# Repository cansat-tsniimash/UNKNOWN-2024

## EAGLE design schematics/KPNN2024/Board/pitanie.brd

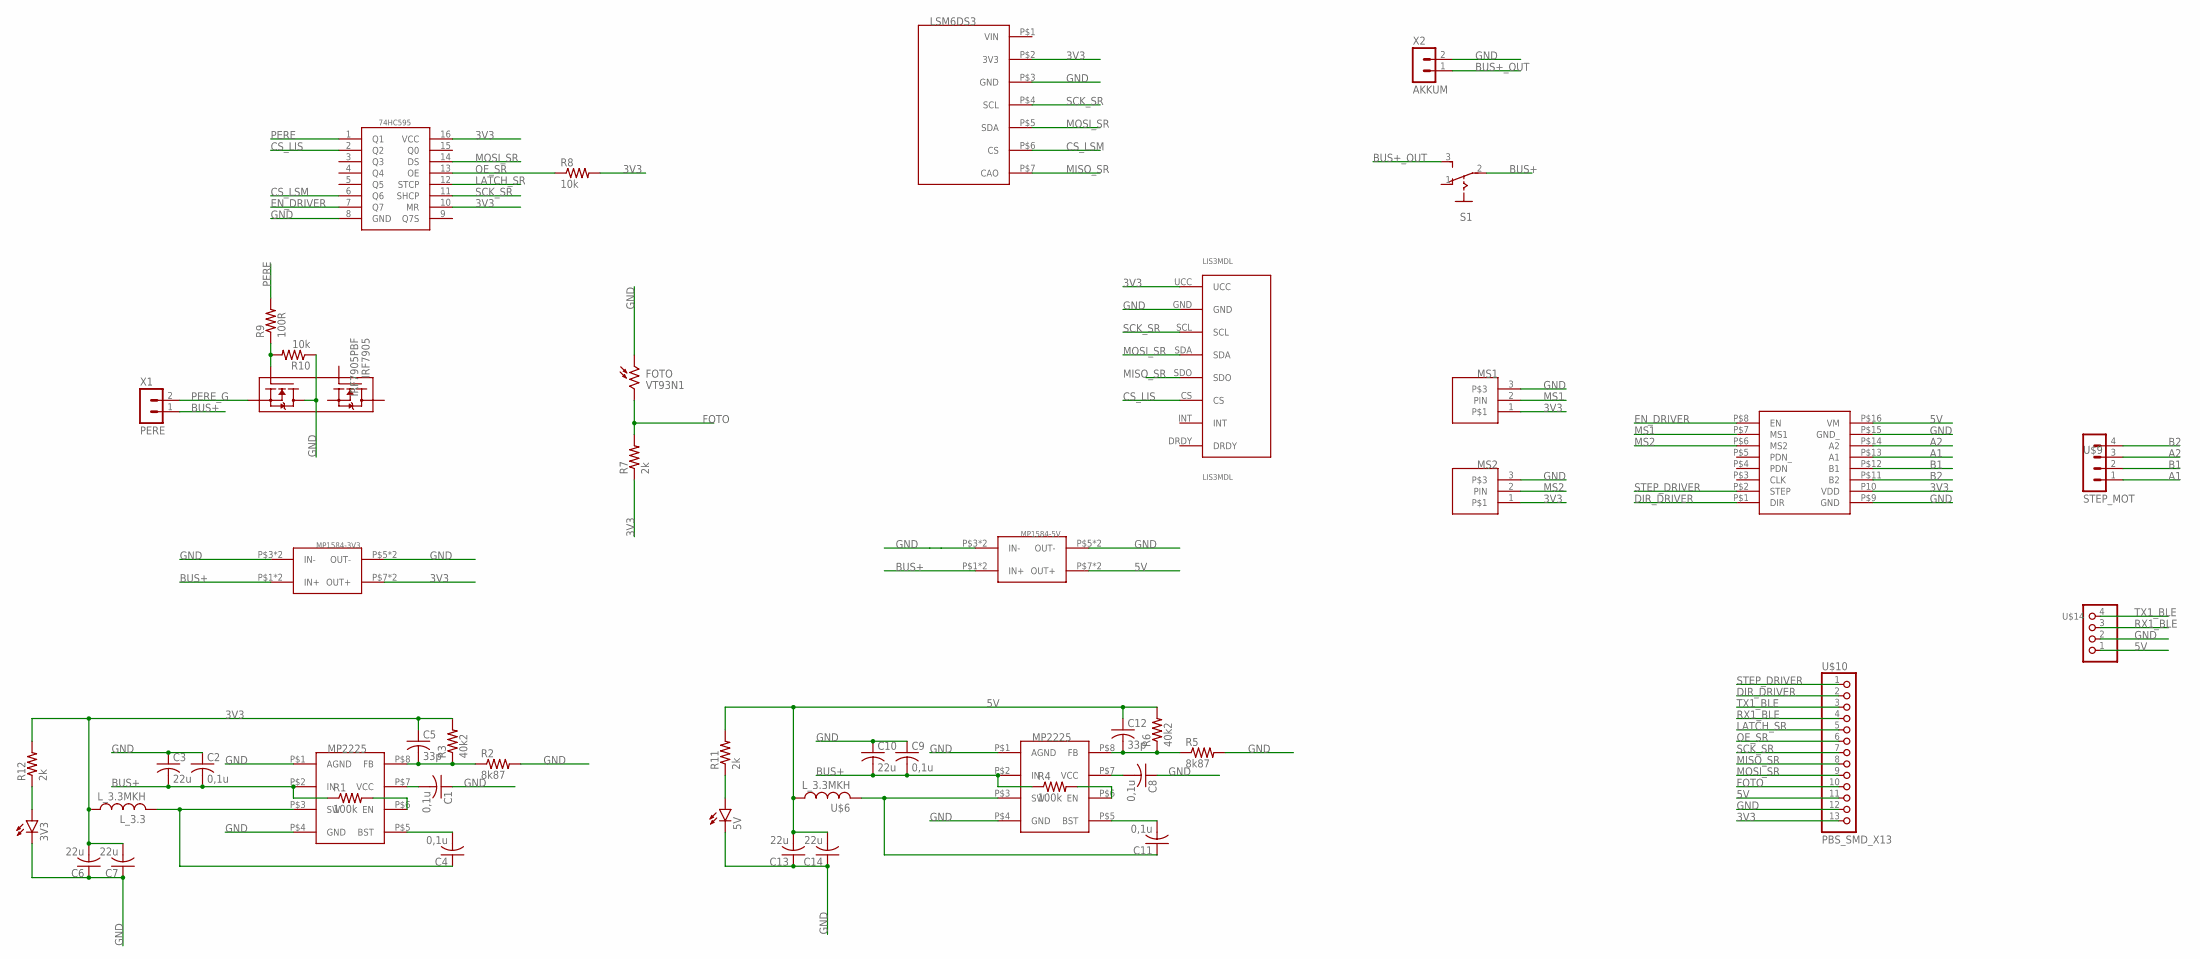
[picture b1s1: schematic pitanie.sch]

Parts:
3V3, 5V: LEDCHIP-LED0603; CHIP-LED0603
74HC595: 74HC595; TSSOP16
C1, C4, C8, C11: 0,1u; C0603
C2, C9: 0,1u; C1206
C3, C10: 22u; C0603
C5, C12: 33p; C0603
C6, C7, C13, C14: 22u; C1206
DRIVER: TMC2209_WITHOUT
FOTO: VT93N1
IRF7905: IRF7905PBF; SO8
LIS3MDL: LIS3MDL
LSM6DS3: LSM6DS3_WITHOUT
L_3.3: L_3.3MKH; L_SPM5020
MP1584-3V3: MP1584-B
MP1584-5V: MP1584; MP1584-B
MS1, MS2: CONNECT_3
R1, R4: 100k; R0603
R2, R5: 8k87; R0603
R3, R6: 40k2; R0603
R7, R11, R12: 2k; R0603
R8, R10: 10k; R0603
R9: 100R; R0603
S1: UNICS-SWITCHSS_12D11; SS_12D11
U$2, U$5: MP2225; TSOT23-8
U$6: L_3.3MKH; L_SPM5020
U$9: STEP_MOT; JST-4-2.5
U$10: PBS_SMD_X13; PBD_SMD_X13
U$14: BLUETOOTH; 53047-04
X1: PERE; JST-2-2.5
X2: AKKUM; JST-2-2.5

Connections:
3V3: 74HC595.10 (MR), 74HC595.16 (VCC), C5.1, C6.2, C7.2, DRIVER.P10 (VDD), LIS3MDL.UCC, LSM6DS3.P$2 (3V3), L_3.3.P$1 (1), MP1584-3V3.P$7 (OUT+), MP1584-3V3.P$8 (OUT+), MS1.1, MS2.1, R3.2, R7.1, R8.2, R12.2, U$10.13
5V: C12.1, C13.2, C14.2, DRIVER.P$16 (VM), MP1584-5V.P$7 (OUT+), MP1584-5V.P$8 (OUT+), R6.2, R11.2, U$6.P$1 (1), U$10.11, U$14.1
A1: DRIVER.P$13 (A1), U$9.1
A2: DRIVER.P$14 (A2), U$9.3
B1: DRIVER.P$12 (B1), U$9.2
B2: DRIVER.P$11 (B2), U$9.4
BUS+: C2.2, C3.2, C9.2, C10.2, MP1584-3V3.P$1 (IN+), MP1584-3V3.P$2 (IN+), MP1584-5V.P$1 (IN+), MP1584-5V.P$2 (IN+), R1.1, R4.1, S1.2, U$2.P$2 (IN), U$5.P$2 (IN), X1.1
BUS+_OUT: S1.3 (S), X2.1
CS_LIS: 74HC595.2 (Q2), LIS3MDL.CS
CS_LSM: 74HC595.6 (Q6), LSM6DS3.P$6 (CS)
DIR_DRIVER: DRIVER.P$1 (DIR), U$10.2
EN_DRIVER: 74HC595.7 (Q7), DRIVER.P$8 (EN)
FOTO: FOTO.P$2 (2), R7.2, U$10.10
GND: 3V3.C, 5V.C, 74HC595.8 (GND), C1.1, C2.1, C3.1, C6.1, C7.1, C8.1, C9.1, C10.1, C13.1, C14.1, DRIVER.P$9 (GND), DRIVER.P$15 (GND_), FOTO.P$1 (1), IRF7905.7 (D2), IRF7905.8 (D2), LIS3MDL.GND, LSM6DS3.P$3 (GND), MP1584-3V3.P$3 (IN-), MP1584-3V3.P$4 (IN-), MP1584-3V3.P$5 (OUT-), MP1584-3V3.P$6 (OUT-), MP1584-5V.P$3 (IN-), MP1584-5V.P$4 (IN-), MP1584-5V.P$5 (OUT-), MP1584-5V.P$6 (OUT-), MS1.3, MS2.3, R2.2, R5.2, R10.1, U$2.P$1 (AGND), U$2.P$4 (GND), U$5.P$1 (AGND), U$5.P$4 (GND), U$10.12, U$14.2, X2.2
LATCH_SR: 74HC595.12 (STCP), U$10.5
MISO_SR: LIS3MDL.SDO, LSM6DS3.P$7 (CAO), U$10.8
MOSI_SR: 74HC595.14 (DS), LIS3MDL.SDA, LSM6DS3.P$5 (SDA), U$10.9
MS1: DRIVER.P$7 (MS1), MS1.2 (PIN)
MS2: DRIVER.P$6 (MS2), MS2.2 (PIN)
unnamed: C1.2, U$2.P$7 (VCC)
unnamed: R1.2, U$2.P$6 (EN)
unnamed: C4.2, U$2.P$5 (BST)
unnamed: C4.1, L_3.3.P$2 (2), U$2.P$3 (SW)
unnamed: C5.2, R2.1, R3.1, U$2.P$8 (FB)
unnamed: IRF7905.2 (G2), R9.1, R10.2
unnamed: C8.2, U$5.P$7 (VCC)
unnamed: R4.2, U$5.P$6 (EN)
unnamed: C11.2, U$5.P$5 (BST)
unnamed: C11.1, U$5.P$3 (SW), U$6.P$2 (2)
unnamed: C12.2, R5.1, R6.1, U$5.P$8 (FB)
unnamed: 5V.A, R11.1
unnamed: 3V3.A, R12.1
OE_SR: 74HC595.13 (OE), R8.1, U$10.6
PERE: 74HC595.1 (Q1), R9.2
PERE_G: IRF7905.1 (S2), X1.2
RX1_BLE: U$10.4, U$14.3
SCK_SR: 74HC595.11 (SHCP), LIS3MDL.SCL, LSM6DS3.P$4 (SCL), U$10.7
STEP_DRIVER: DRIVER.P$2 (STEP), U$10.1
TX1_BLE: U$10.3, U$14.4

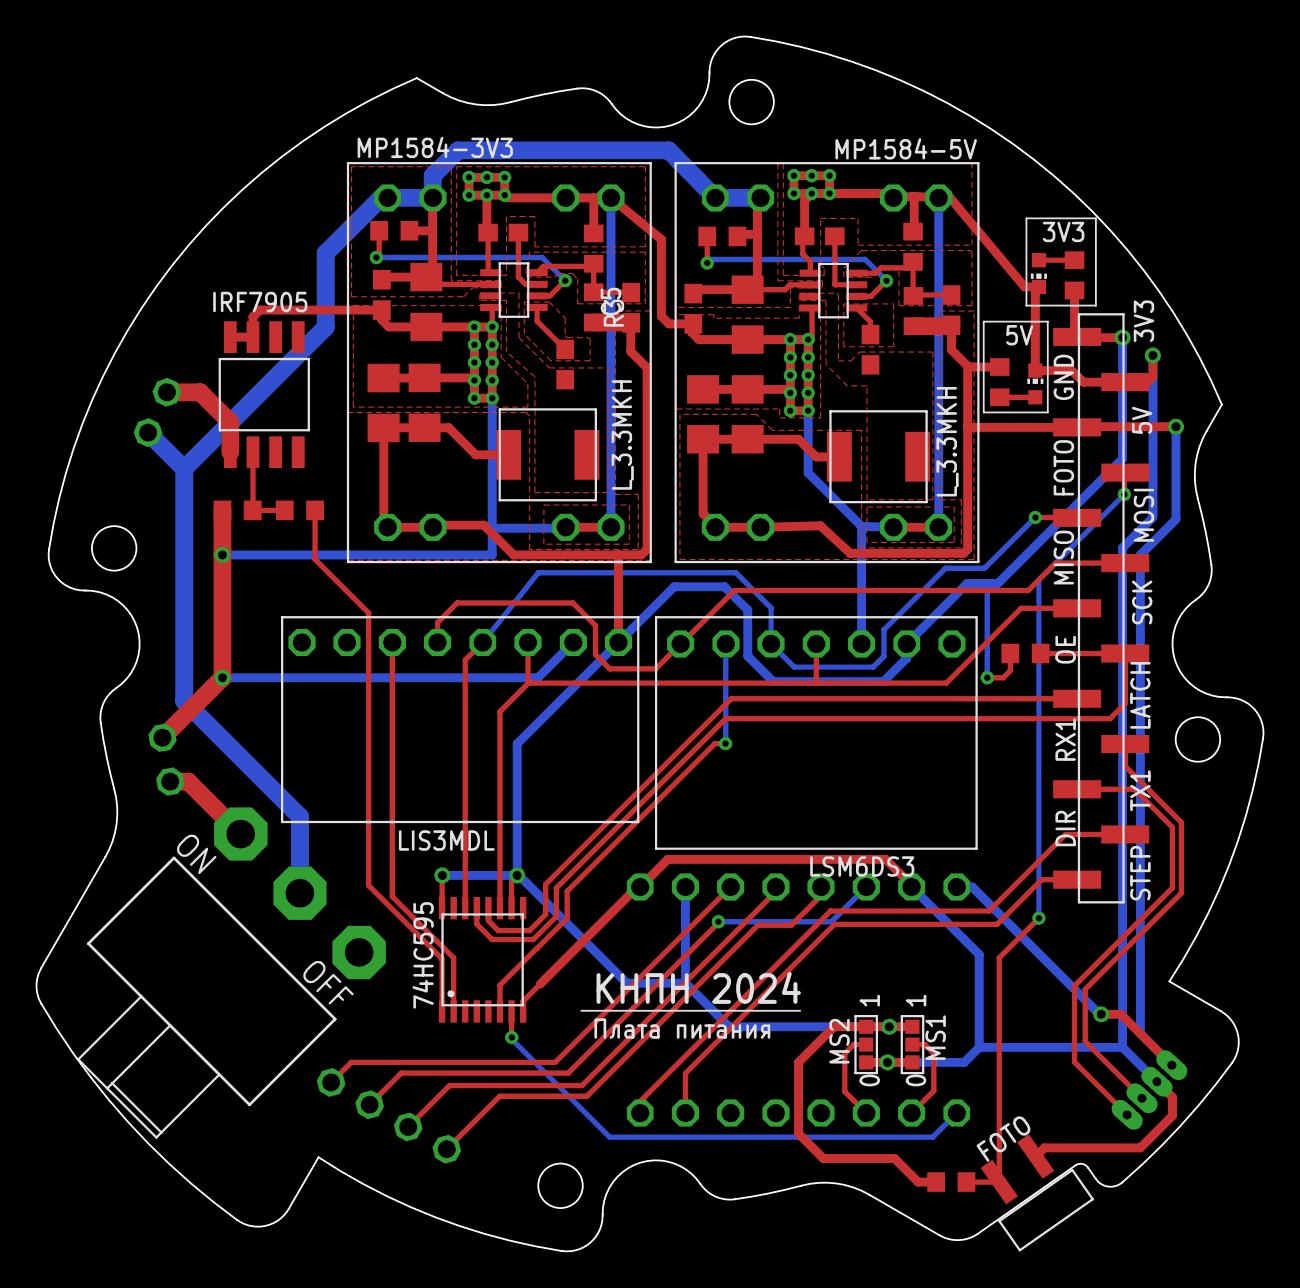
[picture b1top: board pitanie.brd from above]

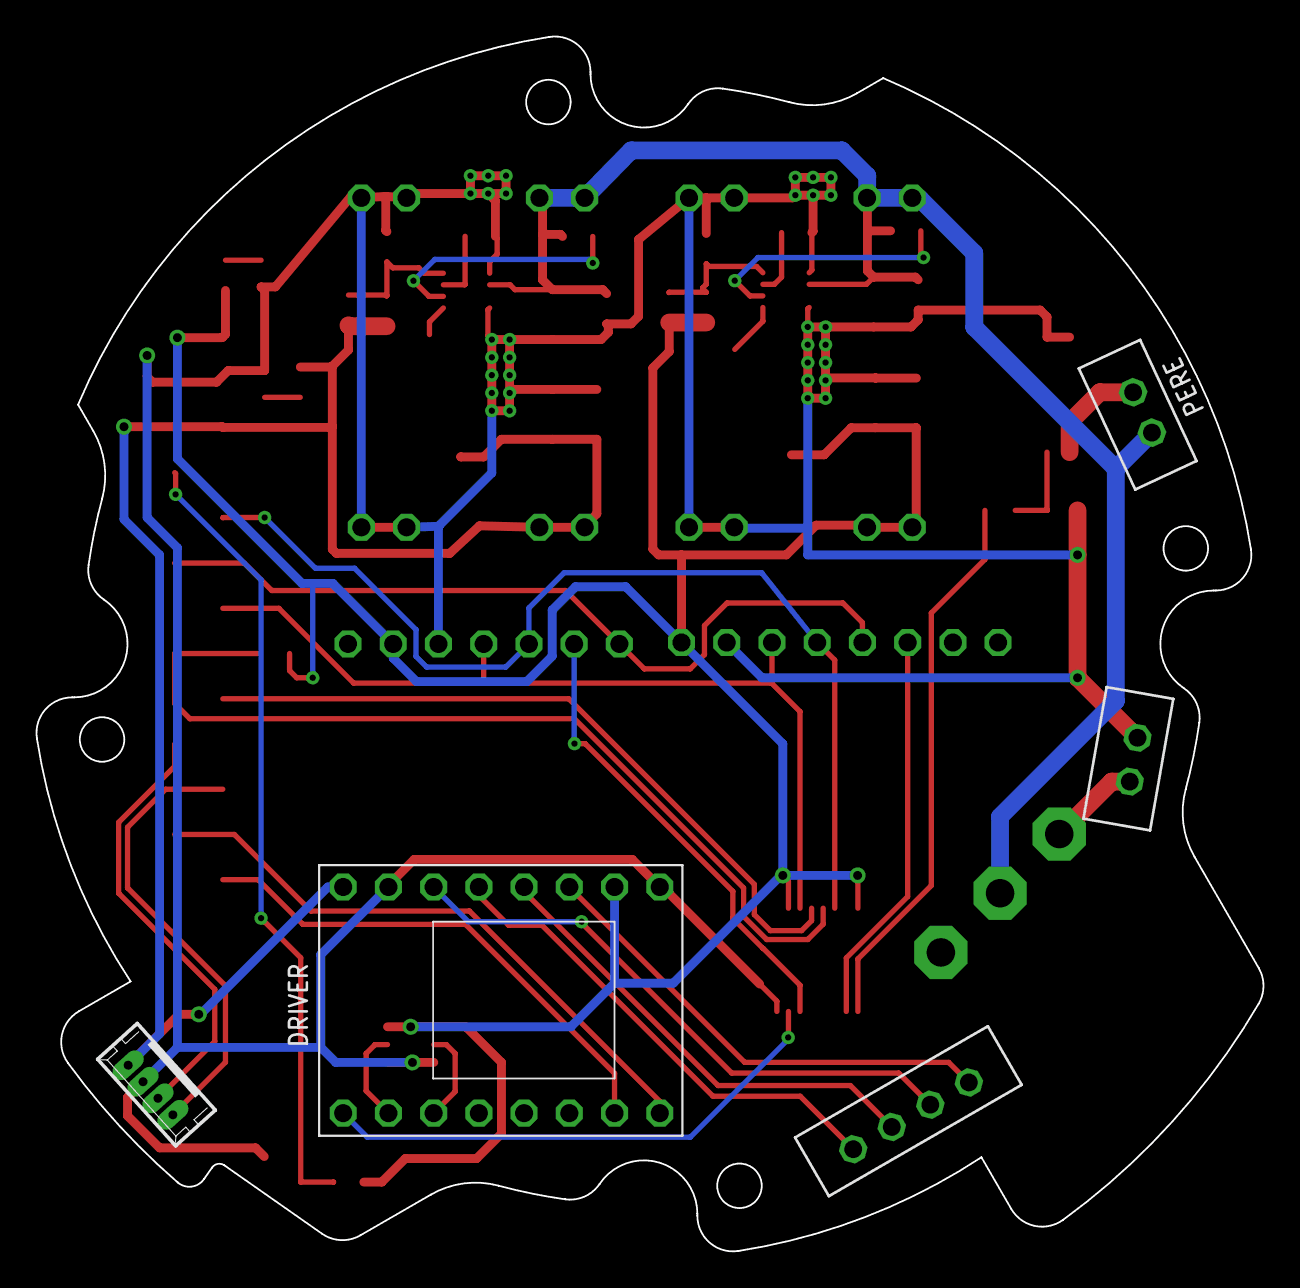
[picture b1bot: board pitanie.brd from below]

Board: 2 copper layers, 68.9 x 68.2 mm, 49 parts (5 on the bottom side), 39 nets.

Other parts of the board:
U$1: Плата питания; LOGO

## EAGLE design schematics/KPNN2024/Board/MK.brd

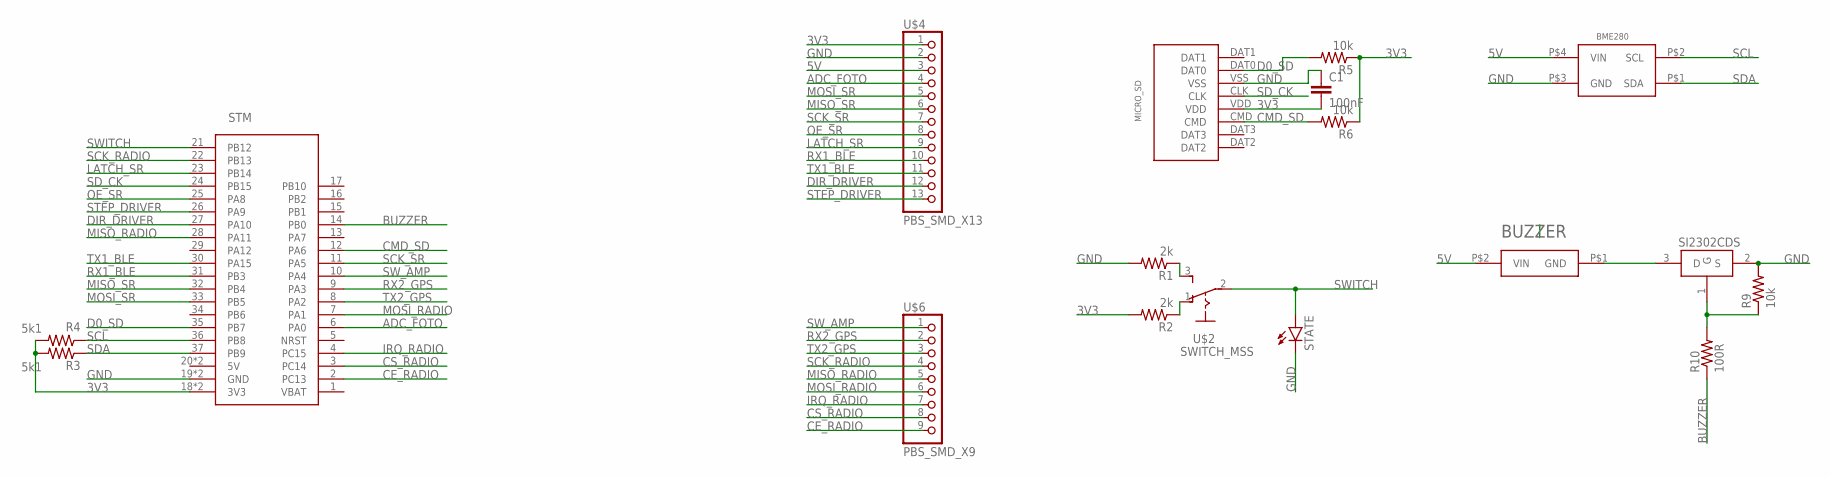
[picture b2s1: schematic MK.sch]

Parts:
BME280: BME280BME280-PINS-ONLY; BME280-PINS-ONLY
BUZZER: BUZZERS8R6; BUZZER-S8R12
C1: 100nF; C0603
MICRO_SD: SD
R1, R2: 2k; R0603
R3, R4: 5k1; R0603
R5, R6, R9: 10k; R0603
R10: 100R; R0603
SI2302CDS: SI2302CDS; SOT23-3
STATE: LEDCHIPLED_0603; CHIPLED_0603
STM: STM32F411_BOARD
U$2: SWITCH_MSS
U$4: PBS_SMD_X13; PBD_SMD_X13
U$6: PBS_SMD_X9

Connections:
3V3: C1.2, MICRO_SD.VDD, R2.2, R3.2, R4.2, R5.1, R6.1, STM.18 (3V3), STM.40 (3V3), U$4.1
5V: BME280.P$4 (VIN), BUZZER.P$2 (VIN), U$4.3
ADC_FOTO: STM.6 (PA0), U$4.4
BUZZER: R10.1, STM.14 (PB0)
CE_RADIO: STM.2 (PC13), U$6.9
CMD_SD: MICRO_SD.CMD, R6.2, STM.12 (PA6)
CS_RADIO: STM.3 (PC14), U$6.8
D0_SD: MICRO_SD.DAT0, R5.2, STM.35 (PB7)
DIR_DRIVER: STM.27 (PA10), U$4.12
GND: BME280.P$3 (GND), C1.1, MICRO_SD.VSS, R1.2, R9.2, SI2302CDS.2 (S), STATE.C, STM.19 (GND), STM.39 (GND), U$4.2
IRQ_RADIO: STM.4 (PC15), U$6.7
LATCH_SR: STM.23 (PB14), U$4.9
MISO_RADIO: STM.28 (PA11), U$6.5
MISO_SR: STM.32 (PB4), U$4.6
MOSI_RADIO: STM.7 (PA1), U$6.6
MOSI_SR: STM.33 (PB5), U$4.5
unnamed: R1.1, U$2.3 (S)
unnamed: R2.1, U$2.1 (O)
unnamed: BUZZER.P$1 (GND), SI2302CDS.3 (D)
unnamed: R9.1, R10.2, SI2302CDS.1 (G)
OE_SR: STM.25 (PA8), U$4.8
RX1_BLE: STM.31 (PB3), U$4.10
RX2_GPS: STM.9 (PA3), U$6.2
SCK_RADIO: STM.22 (PB13), U$6.4
SCK_SR: STM.11 (PA5), U$4.7
SCL: BME280.P$2 (SCL), R4.1, STM.36 (PB8)
SDA: BME280.P$1 (SDA), R3.1, STM.37 (PB9)
SD_CK: MICRO_SD.CLK, STM.24 (PB15)
STEP_DRIVER: STM.26 (PA9), U$4.13
SWITCH: STATE.A, STM.21 (PB12), U$2.2
SW_AMP: STM.10 (PA4), U$6.1
TX1_BLE: STM.30 (PA15), U$4.11
TX2_GPS: STM.8 (PA2), U$6.3

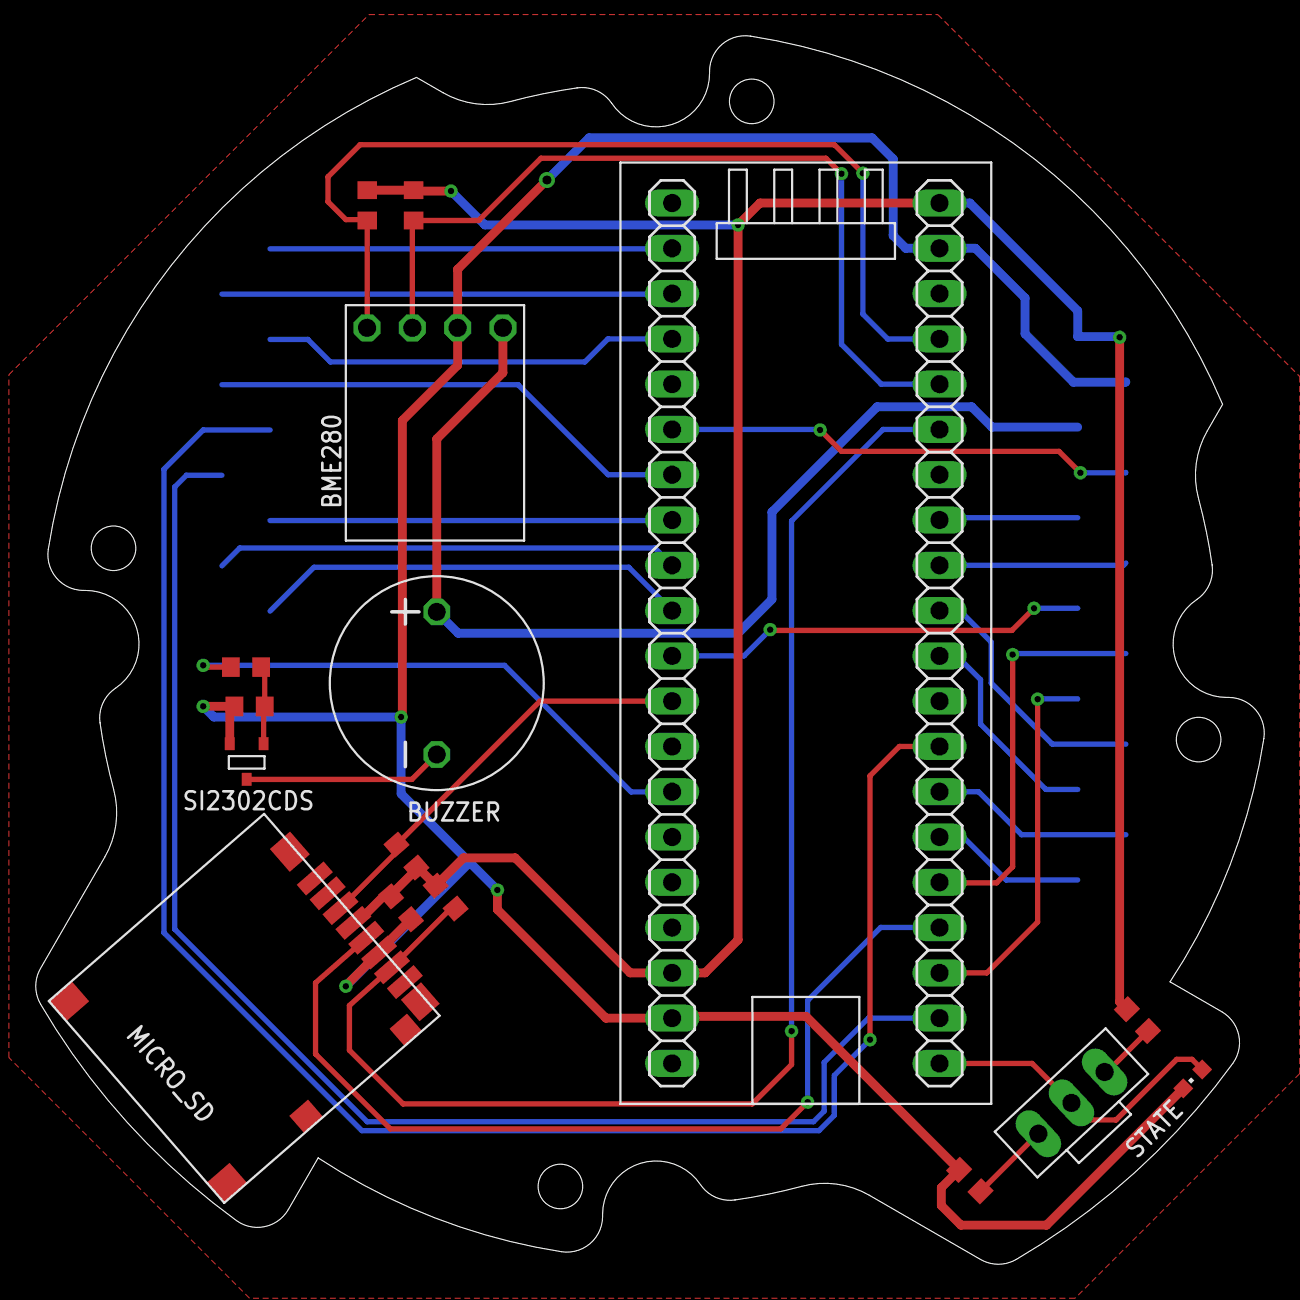
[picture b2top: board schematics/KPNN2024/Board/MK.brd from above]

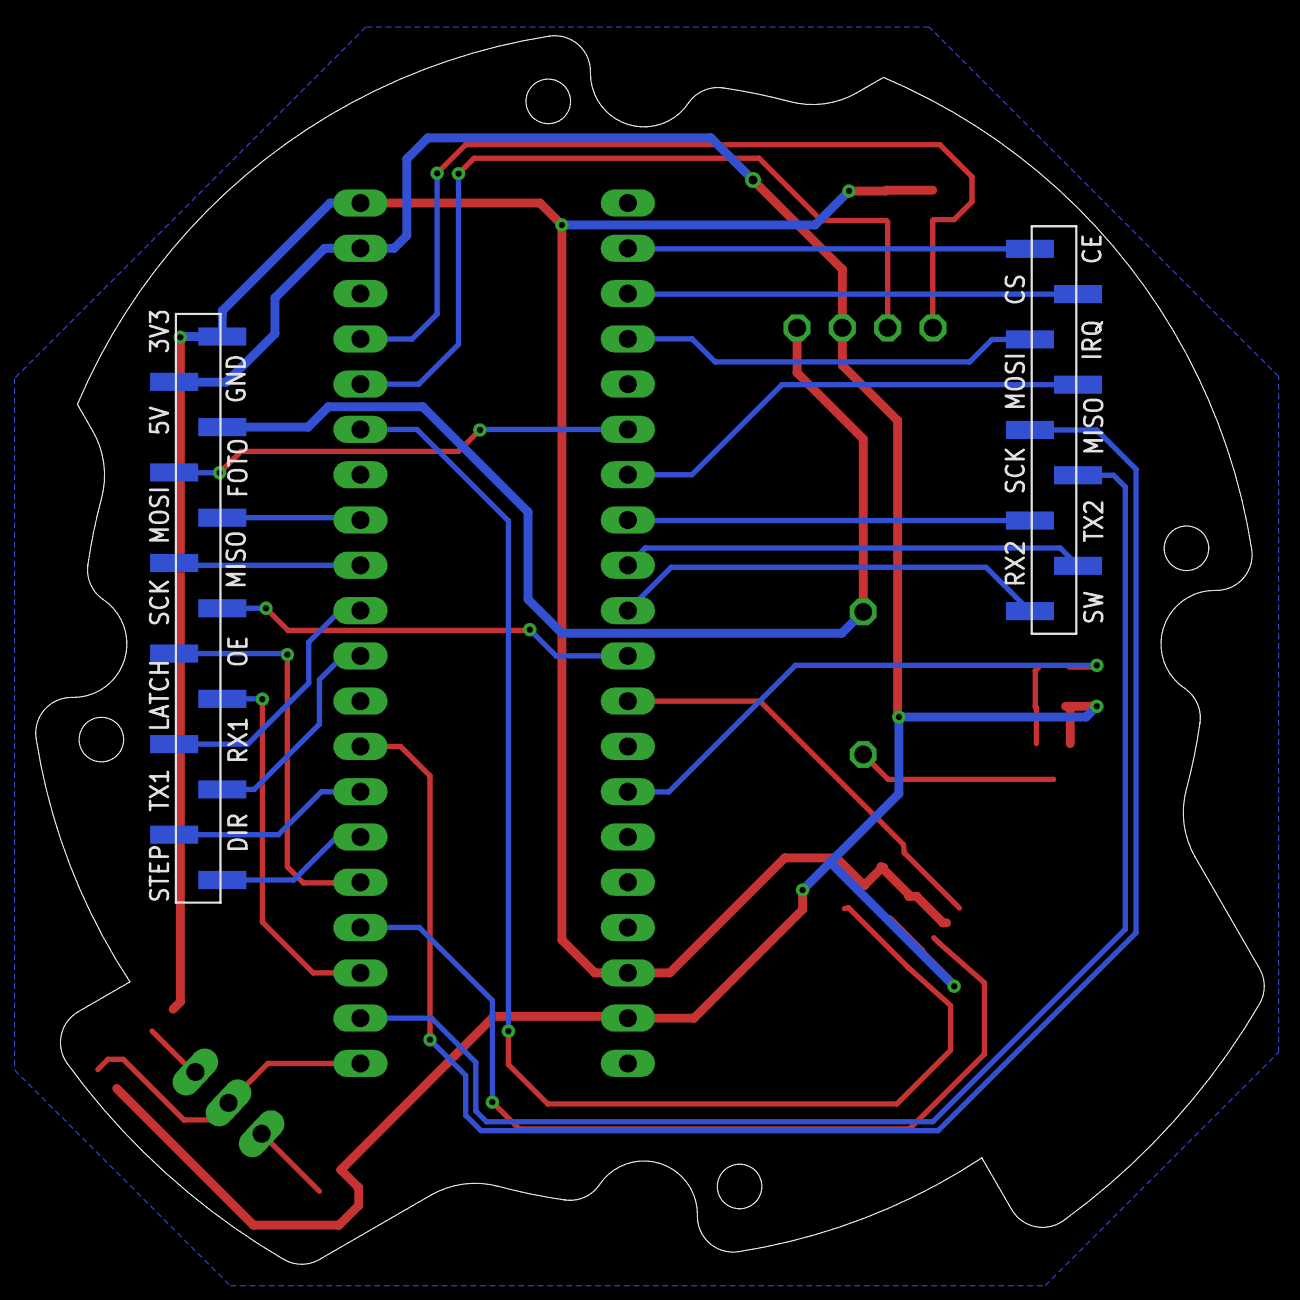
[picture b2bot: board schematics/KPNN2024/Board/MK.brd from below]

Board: 2 copper layers, 68.9 x 68.9 mm, 18 parts (2 on the bottom side), 33 nets.

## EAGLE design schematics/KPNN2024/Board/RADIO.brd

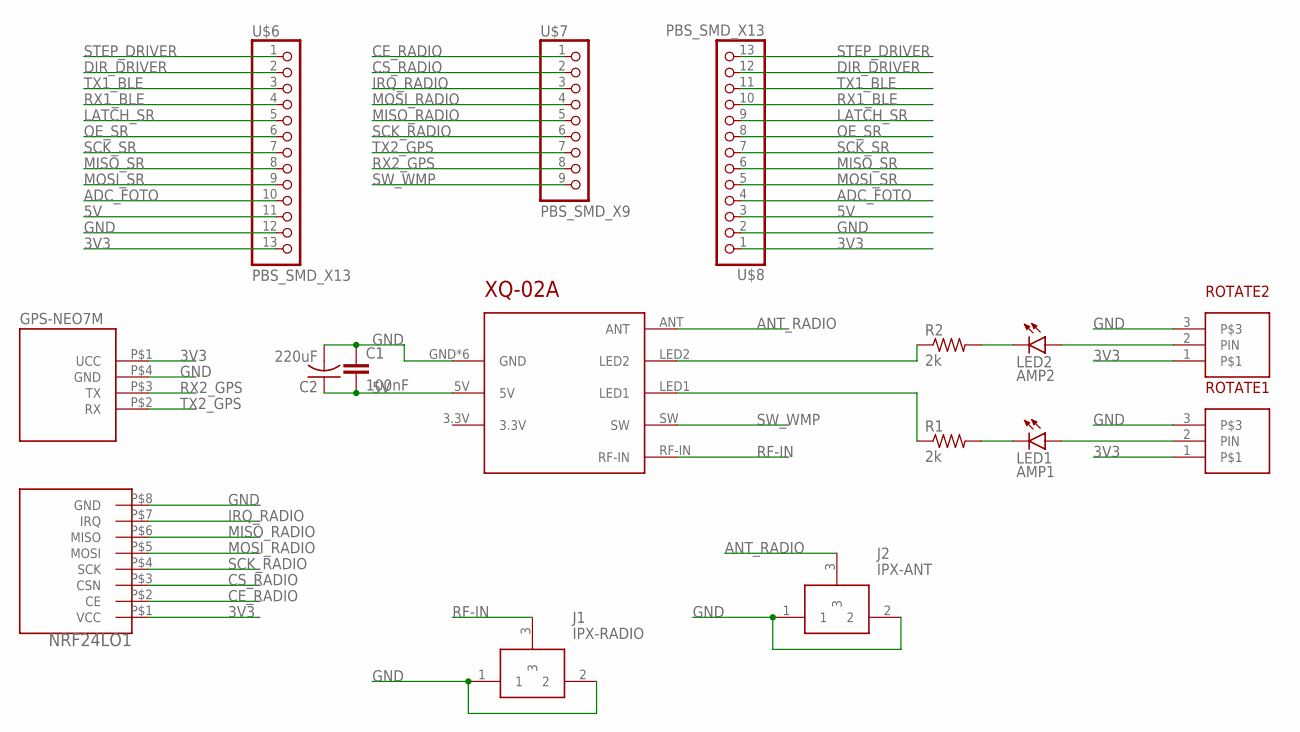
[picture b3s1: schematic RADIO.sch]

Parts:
C1: 100nF; C0603
C2: 220uF; ECAP220-CMD
GPS-NEO7M: GPS-NEO7M
J1: IPX-RADIO; U.FL-R-SMT-1(10)
J2: IPX-ANT; U.FL-R-SMT-1(10)
LED1: AMP1; CHIPLED_0603
LED2: AMP2; CHIPLED_0603
NRF24LO1: NRF24L01_ML01SP4
R1, R2: 2k; R0603
ROTATE1, ROTATE2: CONNECT_3
U$6, U$8: PBS_SMD_X13; PBD_SMD_X13
U$7: PBS_SMD_X9
XQ-02A: XQ-02A

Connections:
3V3: GPS-NEO7M.P$1 (UCC), NRF24LO1.P$1 (VCC), ROTATE1.1, ROTATE2.1, U$6.13, U$8.1
5V: C1.2, C2.P$1 (1), U$6.11, U$8.3, XQ-02A.5V
ADC_FOTO: U$6.10, U$8.4
ANT_RADIO: J2.3, XQ-02A.ANT
CE_RADIO: NRF24LO1.P$2 (CE), U$7.1
CS_RADIO: NRF24LO1.P$3 (CSN), U$7.2
DIR_DRIVER: U$6.2, U$8.12
GND: C1.1, C2.P$2 (2), GPS-NEO7M.P$4 (GND), J1.1, J1.2, J2.1, J2.2, NRF24LO1.P$8 (GND), ROTATE1.3, ROTATE2.3, U$6.12, U$8.2, XQ-02A.GND, XQ-02A.GND1 (GND), XQ-02A.GND2 (GND), XQ-02A.GND3 (GND), XQ-02A.GND4 (GND), XQ-02A.GND5 (GND)
IRQ_RADIO: NRF24LO1.P$7 (IRQ), U$7.3
LATCH_SR: U$6.5, U$8.9
MISO_RADIO: NRF24LO1.P$6 (MISO), U$7.5
MISO_SR: U$6.8, U$8.6
MOSI_RADIO: NRF24LO1.P$5 (MOSI), U$7.4
MOSI_SR: U$6.9, U$8.5
unnamed: LED1.C, R1.2
unnamed: LED2.C, R2.2
unnamed: LED1.A, ROTATE1.2 (PIN)
unnamed: LED2.A, ROTATE2.2 (PIN)
unnamed: R2.1, XQ-02A.LED2
unnamed: R1.1, XQ-02A.LED1
OE_SR: U$6.6, U$8.8
RF-IN: J1.3, XQ-02A.RF-IN
RX1_BLE: U$6.4, U$8.10
RX2_GPS: GPS-NEO7M.P$3 (TX), U$7.8
SCK_RADIO: NRF24LO1.P$4 (SCK), U$7.6
SCK_SR: U$6.7, U$8.7
STEP_DRIVER: U$6.1, U$8.13
SW_WMP: U$7.9, XQ-02A.SW
TX1_BLE: U$6.3, U$8.11
TX2_GPS: GPS-NEO7M.P$2 (RX), U$7.7

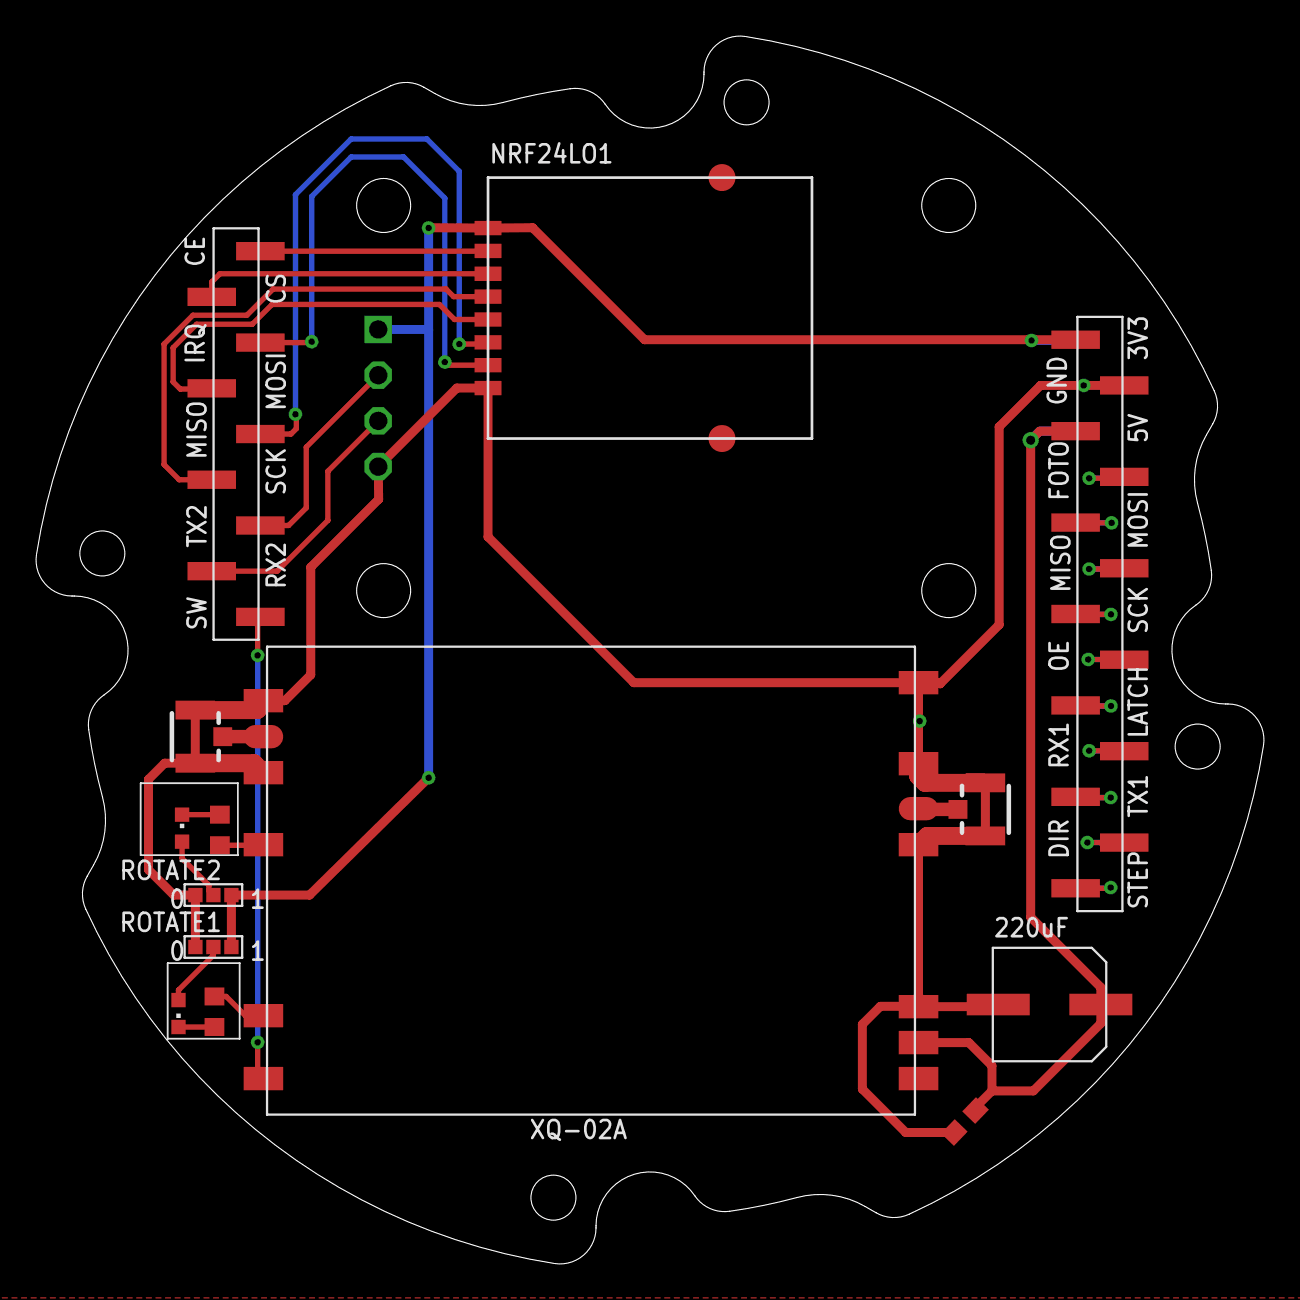
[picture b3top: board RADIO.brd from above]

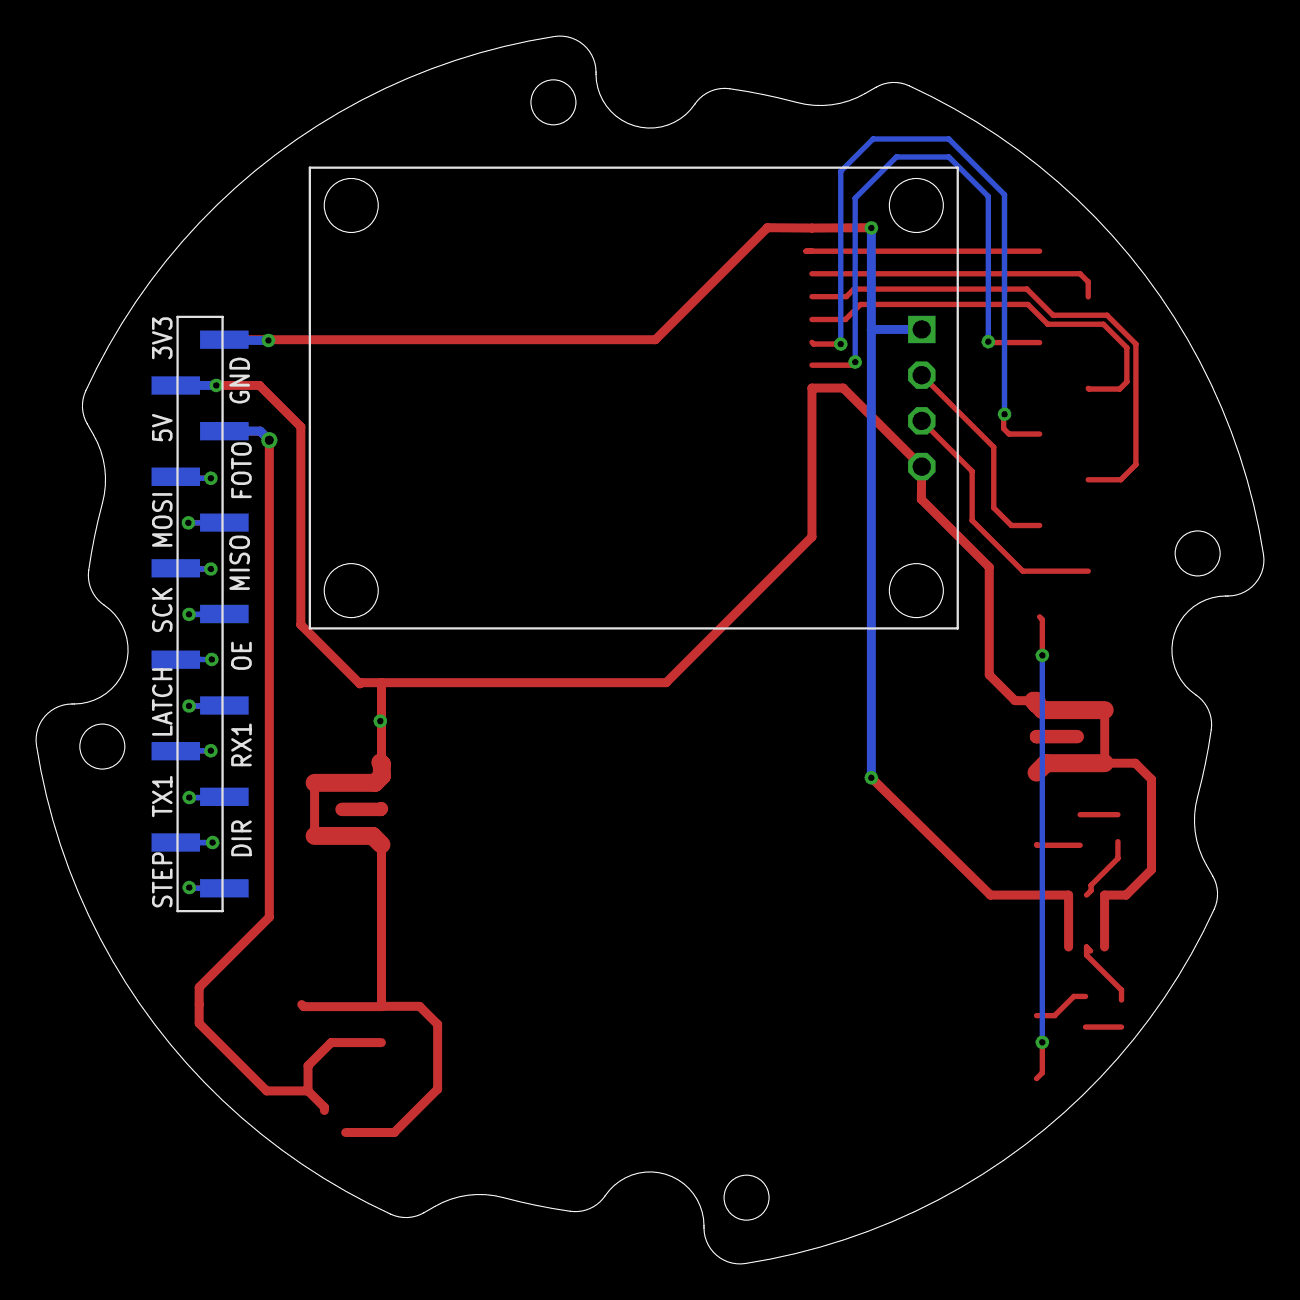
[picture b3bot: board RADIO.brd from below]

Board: 2 copper layers, 68.2 x 68.2 mm, 16 parts (2 on the bottom side), 30 nets.

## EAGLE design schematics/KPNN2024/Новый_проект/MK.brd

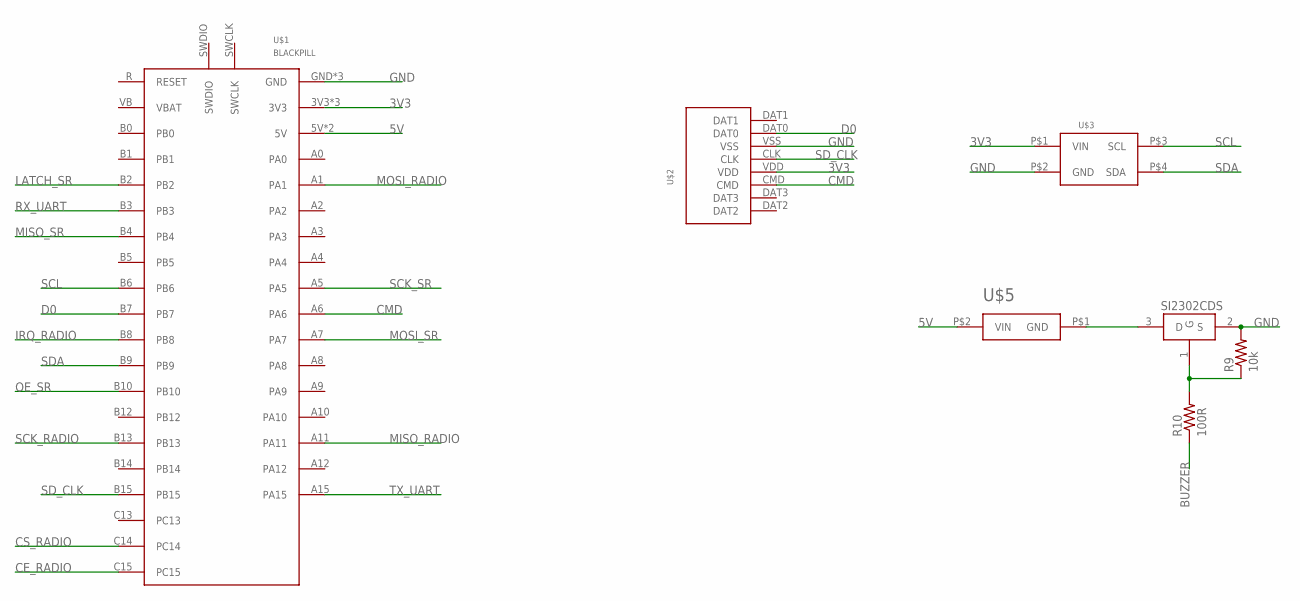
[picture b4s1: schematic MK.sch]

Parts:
R9: 10k; R0603
R10: 100R; R0603
U$1: BLACKPILL
U$2: SD
U$3: BME280
U$5: BUZZERS8R6; BUZZER-S8R12
U$20: SI2302CDS; SOT23-3

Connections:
3V3: U$1.3V3, U$1.3V31 (3V3), U$1.3V32 (3V3), U$2.VDD, U$3.P$1 (VIN)
5V: U$1.5V, U$1.5V1 (5V), U$5.P$2 (VIN)
BUZZER: R10.1
CE_RADIO: U$1.C15
CMD: U$1.A6, U$2.CMD
CS_RADIO: U$1.C14
D0: U$1.B7, U$2.DAT0
GND: R9.2, U$1.GND, U$1.GND1 (GND), U$1.GND3 (GND), U$2.VSS, U$3.P$2 (GND), U$20.2 (S)
IRQ_RADIO: U$1.B8
LATCH_SR: U$1.B2
MISO_RADIO: U$1.A11
MISO_SR: U$1.B4
MOSI_RADIO: U$1.A1
MOSI_SR: U$1.A7
unnamed: U$5.P$1 (GND), U$20.3 (D)
unnamed: R9.1, R10.2, U$20.1 (G)
OE_SR: U$1.B10
RX_UART: U$1.B3
SCK_RADIO: U$1.B13
SCK_SR: U$1.A5
SCL: U$1.B6, U$3.P$3 (SCL)
SDA: U$1.B9, U$3.P$4 (SDA)
SD_CLK: U$1.B15, U$2.CLK
TX_UART: U$1.A15

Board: 2 copper layers, 7 parts (0 on the bottom side), 10 nets, no tracks yet.

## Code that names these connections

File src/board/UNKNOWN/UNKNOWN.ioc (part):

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Mcu.Name=STM32F411C(C-E)Ux
Mcu.Package=UFQFPN48
Mcu.UserName=STM32F411CEUx
PA0-WKUP.Signal=ADCx_IN0
PA1.Mode=Full_Duplex_Master
PA1.Signal=SPI4_MOSI
PA10.GPIOParameters=GPIO_Label
PA10.GPIO_Label=step
PA10.Signal=GPIO_Output
PA11.Mode=Full_Duplex_Master
PA11.Signal=SPI4_MISO
PA13.Mode=Serial_Wire
PA13.Signal=SYS_JTMS-SWDIO
PA14.Mode=Serial_Wire
PA14.Signal=SYS_JTCK-SWCLK
PA15.Mode=Asynchronous
PA15.Signal=USART1_TX
PA2.Mode=Asynchronous
PA2.Signal=USART2_TX
PA3.Mode=Asynchronous
PA3.Signal=USART2_RX
PA4.Signal=GPIO_Input
PA5.Mode=Full_Duplex_Master
PA5.Signal=SPI1_SCK
PA6.Mode=SD_1_bit
PA6.Signal=SDIO_CMD
PA8.GPIOParameters=GPIO_Label
PA8.GPIO_Label=oe
PA8.Signal=GPIO_Output
PA9.GPIOParameters=GPIO_Label
PA9.GPIO_Label=dir
PA9.Signal=GPIO_Output
PB0.Signal=GPIO_Output
PB12.Signal=GPIO_Input
PB13.Mode=Full_Duplex_Master
PB13.Signal=SPI4_SCK
PB14.GPIOParameters=GPIO_Label
PB14.GPIO_Label=latch
PB14.Signal=GPIO_Output
PB15.Mode=SD_1_bit
PB15.Signal=SDIO_CK
PB3.Mode=Asynchronous
PB3.Signal=USART1_RX
PB4.Mode=Full_Duplex_Master
PB4.Signal=SPI1_MISO
PB5.Mode=Full_Duplex_Master
PB5.Signal=SPI1_MOSI
PB7.Mode=SD_1_bit
PB7.Signal=SDIO_D0
PB8.Mode=I2C
PB8.Signal=I2C1_SCL
PB9.Mode=I2C
PB9.Signal=I2C1_SDA
PC13-ANTI_TAMP.GPIOParameters=GPIO_Label
PC13-ANTI_TAMP.GPIO_Label=ce
PC13-ANTI_TAMP.Signal=GPIO_Output
PC14-OSC32_IN.GPIOParameters=GPIO_Label
PC14-OSC32_IN.GPIO_Label=cs
PC14-OSC32_IN.Signal=GPIO_Output
PC15-OSC32_OUT.GPIOParameters=GPIO_Label
PC15-OSC32_OUT.GPIO_Label=irq
PC15-OSC32_OUT.Signal=GPIO_Input
RCC.HSE_VALUE=25000000
RCC.SYSCLKFreq_VALUE=80000000
RCC.SYSCLKSource=RCC_SYSCLKSOURCE_PLLCLK
board=custom

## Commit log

2023-09-23 Создали репозиторий
2023-09-23 UNKNOWN 2024 НАЧАЛО КОНЦА
2023-09-23 сделал интересный и необычный датчик mq2))
2023-09-23 ПАХАЛ 6 ЧАСОВ, ДЕЛАЛ МОДЕЛМ ДАТЧИКОВ
2023-09-27 какие-то модели и сборка в крео
2023-09-27 какие-то модели и сборка в крео(и ещё чёто Ромино тут)
2023-09-30 я устал и хочу есть
2023-09-30 удалил дебаг хахаха он лох
2023-09-30 сделал больше, чем за прошлые 29 дней
2023-09-30 СД РАБОТАЕТ УРААААА А ЕЩЕ У МЕНЯ НА ПК МИНЬЕН В ФОРМЕ БАРСЫ УРА
2023-10-04 ГПС РАБОТАЕТ НУ КУКИ ПОЙМАЛ ФИКСЫ НЕДАЛЕКО ЭЩКЕРЕЕ
2023-10-06 написал радио по жести хз работает или нет
2023-10-07 Добавила старую наземку в папку
2023-10-11 чето с наземкой сделал
2023-10-13 хз чо
2023-10-14 новая наземка
2023-10-21 сделал почвы
2023-10-21 ПОМЕНЯЛ SPI ОНО РАБОТАЕТ ЕЕЕЕЕЕ РОМА ЛОХ
2023-10-27 марина с машей чето сделали а я такой типа zzzzzzzz(сплю)
2023-10-27 забыл чё делал сорри
2023-10-27 начал делать конструкцию подъёмного механизма Артемий лох
2023-10-28 добавил двойку в коде(сд не работало из за питания)
2023-10-28 я ничего не понимаю
2023-11-01 чиню радио
2023-11-03 чето
2023-11-04 Добавил ину работает скорее всего правильно все по кайфу есть же ЭЩКЕРЕ
2023-11-05 начали моделить ветрогенератор
2023-11-08 Поменяла имя файла винта
2023-11-08 я пока что ничё не сделал
2023-12-13 верх да
2023-12-13 Марина можно домой
2023-12-13 я хз чё это
2023-12-13 палка с дырками и кружок без дырок
2023-12-15 жёстко наработал целых 3 кружка и прикрепил на них модели
2023-12-16 патч на аппарат, добавили 15 новых моделей
2023-12-16 сделал верхний корпус
2023-12-20 ИЛЬЯ БЕЗДАРЬ
2023-12-22 Добавил колодки на платы
2023-12-23 плата
2023-12-23 Разъемы smd
2023-12-23 awe3srdtyughojikp
2023-12-23 Исправлены smd разъемы
2023-12-23 Сделала сборку плат
2023-12-23 GPS теперь крепится на плату
2023-12-23 edxc ftnhju7mp;,.
2023-12-27 ПОКРАСИЛ ПЛАТЫ УРА
2023-12-27 представте тут нормальное название комита
2023-12-27 ещё более комитный комит
2023-12-29 сделал механизмы
2023-12-30 новый год еееееееееееееееееееееееееееееееееееууууууууууууууууу
2024-01-07 доделали сборку, создали разнесенный вид оптического модуля
2024-01-09 чёто сделал
2024-01-10 вабулабудабдаб
2024-01-17 всфывйцв
2024-01-19 1234567890
2024-01-24 если у футболиста отобрать мяч он сменит профессию, если у художника отобрать кисть он захватит половину европы
2024-01-24 йцукенгшщзхъ
2024-01-31 Добавлена модель плана полета и файлы для презентации
2024-01-31 падаби папирипупу пим папирипу
2024-01-31 ПОМЕЛО
2024-01-31 добавил маджвик эщкерееее
2024-01-31 Добавлены файлы на ЗС
2024-02-01 Изменена модель и файлы ЗС
2024-02-02 сд чета какашка
2024-02-03 тат конкретный +вайб
2024-02-07 Добавлены УГО радио и разъемов радиолинии
2024-02-07 шкибиди доп доп доп доп ес ес ес ес шкиб шкибиди дип шкибиди добиди добиди
2024-02-07 Даня верни клей
2024-02-07 Добавлен скрипт Маджвика с моделью
2024-02-09 Добавлена плата питания
2024-02-09 swag
2024-02-10 Добавлены контура плат
2024-02-10 Вабба Лабба Даб Даб
2024-02-10 норм
2024-02-10 я смотрел рика и морти вместо работать
2024-02-10 я тоже
2024-02-14 ааа платы платы полигоны разводка платы ааааа
2024-02-16 авыпльдыф
2024-02-17 начало наземки
2024-02-17 добавлены смд разъемы для плат
2024-02-17 плата радио
2024-02-17 разъемы смд
2024-02-17 разъемы еще
2024-02-17 amogus
2024-02-20 изменил пару вещей в реале хз как
2024-02-21 кцуенгшщозлдх
2024-02-21 плата МК под разводку
2024-02-21 отртамгор
2024-02-21 горншлщ90зд-жхэзжотрм с
2024-02-21 рома гад смёрджил мой коммит :(
2024-02-21 `1234567890000-=qwertyuiop[]asdfghjkl;'zxcvbnm,./
2024-02-21 плата рпарпарпараарпарпарпааарпарпарпауекуекуекусруркра
2024-02-21 чучуть подправил норм
2024-02-23 sdfghgfds
2024-02-23 'эщкере
2024-02-24 артемий сколько можно мерджить комиты зачем мы тогда стараемся над нашими шедевральными названиями
2024-02-24 когда фондю?
2024-02-24 Добавлены разъемы на плату питания
2024-02-24 плата питания удалена
2024-02-24 плата питания возвращена
2024-02-24 добавлены стл корпусных деталей
2024-02-24 ывавп лыл
2024-02-24 поменял пины создал функцию поворота
2024-02-25 Разведена плата питания
2024-02-28 тцилизьм
2024-02-28 драйвер на шд кайф
2024-02-28 ждангнгорлек самолзшщапнготреап ияч пнгеапорвап тапоршл
2024-02-29 Платы вроде готовы
2024-02-29 буэээ
2024-03-01 raspberry and servo
2024-03-01 ййййййййййййййййййййййййййййййййййй
2024-03-02 печать крышек
2024-03-02 сдклвл платы а мботрен зз
2024-03-02 чем гуще лес сел в машину и сгорел
2024-03-02 шел по лесу медведь тем темнее чаща
2024-03-03 поправила платы
2024-03-04 Модели поправлены в соответствии с платами
2024-03-06 щдддоьблллсапмю.ю
2024-03-06 dg4r5th7yujoik9pl;
2024-03-06 зделяльэпочамупробедненежимется оооооооо палучилось
2024-03-06 gfchugyuuhu
2024-03-08 Я очень долго плакал
2024-03-10 Оставьте korpus_top.prt на месте
2024-03-16 без труда то и пожнешь
2024-03-16 Наземка работает. Датчики BME, LSM и LIS - нет(
2024-03-16 лропавыаполджоавпролдрРПАПРОЛД
2024-03-16 ДИРКА
2024-03-16 eщкере
2024-03-16 Поддержки оптического модуля
2024-03-18 Печать нижнего корпуса и половинок оптического модуля.
2024-03-20 наземка 16.03
2024-03-20 trf54y67uio90p-
2024-03-20 скибиди вапапапа скибиди вапапапапа скибиди вапапапапапапапа бум бум скибиди па па
2024-03-21 Теперь шаговик должен влезть
2024-03-23 блин я одну запятую забыл убрать
2024-03-23 прием блютуз
2024-03-23 отправка блютуз и рабочее бме
2024-03-30 нижний корпус повернут в нужное положение
2024-04-01 поправила все
2024-04-05 я сам не понял чё я написал
2024-04-05 пакеты изменил
2024-04-06 уаношлщд
2024-04-09 stl korpus_top
2024-04-10 шд работает и фоторезистор тоже
2024-04-12 блин
2024-04-12 ееее
2024-04-13 Крышка аккума должна быть норм
2024-04-13 serv works
2024-04-13 АААААААААА
2024-04-13 гшвфуп78уф
2024-04-15 fgbnhyjumiolp;
2024-04-16 модель оптического отсека с переключателем
2024-04-19 БББББББББББББББББББ
2024-04-19 чиназес
2024-04-20 пищалка и переключатель работают начал работу с маджвиком и матрицами
2024-04-22 tredrfgyhuj
2024-04-23 стл распберри с гайками
2024-05-06 Добавлен пережигатель, платы повернуты на 90 градусов из-за разъемов
2024-05-10 ну ёмаё
2024-05-11 текущая прошивка
2024-05-11 игагшптдшгщщщщщщщщщщ
2024-05-17 видео норм
2024-05-17 ещкере
2024-05-17 полный эщкере
2024-05-30 гедагади гедагеда го а бин мерит а лон тайм аго
2024-05-30 печать верхнего корпуса, отверстия перенесены
2024-06-01 ывапрлджэ
2024-06-03 печать optical_base
2024-06-05 он вечно все путает он путает все на свету и во тьме он говорит что кажется что что то перепутал и все его любят этого mister Jonson...
2024-06-07 Commit Message
2024-06-07 ну чето сделал
2024-06-08 запись fix на СД, гпс работает, радио перестало
2024-06-08 гпс и радио работают
2024-06-12 серва должна работать
2024-06-15 пук пук
2024-06-15 rgghjklfghjkmldecgfbhjnmkl
2024-06-19 4 пакета + 1 бинарник. Надо ускорять радио
2024-06-20 и еще
2024-06-20 1 сторчка
2024-06-20 gg wp
2024-06-20 while for nrf
2024-06-22 начали парсер
2024-06-22 парсер и ещё какие то штуки которые я наверное должен был закомитить уже давным давно и может быть от этого у вас что-нибудь сломается, но откатите если что так что ничего страшного лол
2024-06-22 rtyuio
2024-06-22 куыенпгршо
2024-06-25 я стоко всего сделал ну стоко это просто жесть у нас теперь работает парсер... ну не то что бы он и раньше не работал, но до этого он не считал контрольную сумму пакетов, а сейчас он её считает. Наве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
2024-06-26 а не, ошибся чёт
2024-06-26 чёт сделал
2024-06-26 Сделал программу, которая симулирует исправный приём телеметрии(на запусках пригодится)
2024-06-26 4re5ty67uio9
2024-06-26 пакеты пакетики пакеточички пакетусики packets
2024-06-27 магнитометр правильный на земле
2024-06-28 поменял 1 цифру
2024-06-29 time_s и time_us по гпс надо писать в пакет, а не только в переменную, Артемий!!! А размер time_us 4 байта, а не 8, Артемий!!! Размер пакетов до 32 байт, а не 35, Артемий!!!
2024-06-29 забыли
2024-06-29 список
2024-06-30 добавлен пакет с вектором и углами
2024-06-30 Маленький бой варнингам и другая система частотной отправки телеметрии
2024-06-30 в обработке свежая телеметрия + добавлен пакет с вектором и углами
2024-07-01 gcs тоже надо менять, Илья!!!
2024-07-02 final comit
2024-07-02 final commit
2024-07-03 если кому интересно я помылся
2024-07-04 ой забыл
2024-07-04 вкусняшка
